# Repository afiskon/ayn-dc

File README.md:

# AYN/DC

QRP CW Transceiver

* Covers 40, 30, 20 and 17 meters
* Easily modifiable for other 4 bands
* DC receiver with sideband suppression
* Simple but effective AGC
* Supports RIT and XIT
* 10-30 WPM Elekey-B type keyer + straight key mode
* Keyer settings are saved in EEPROM
* ~5W class C power amplifier
* Has a VCC indicator and a SWR meter
* PCB is designed to fit into Hammond 1590BB enclosure
* The project is 100% open-source

Links:

* Article (in Russian): https://eax.me/2023/2023-01-16-ayn-dc-transceiver.html
* Demo: https://www.youtube.com/watch?v=9x_RN68QJhk

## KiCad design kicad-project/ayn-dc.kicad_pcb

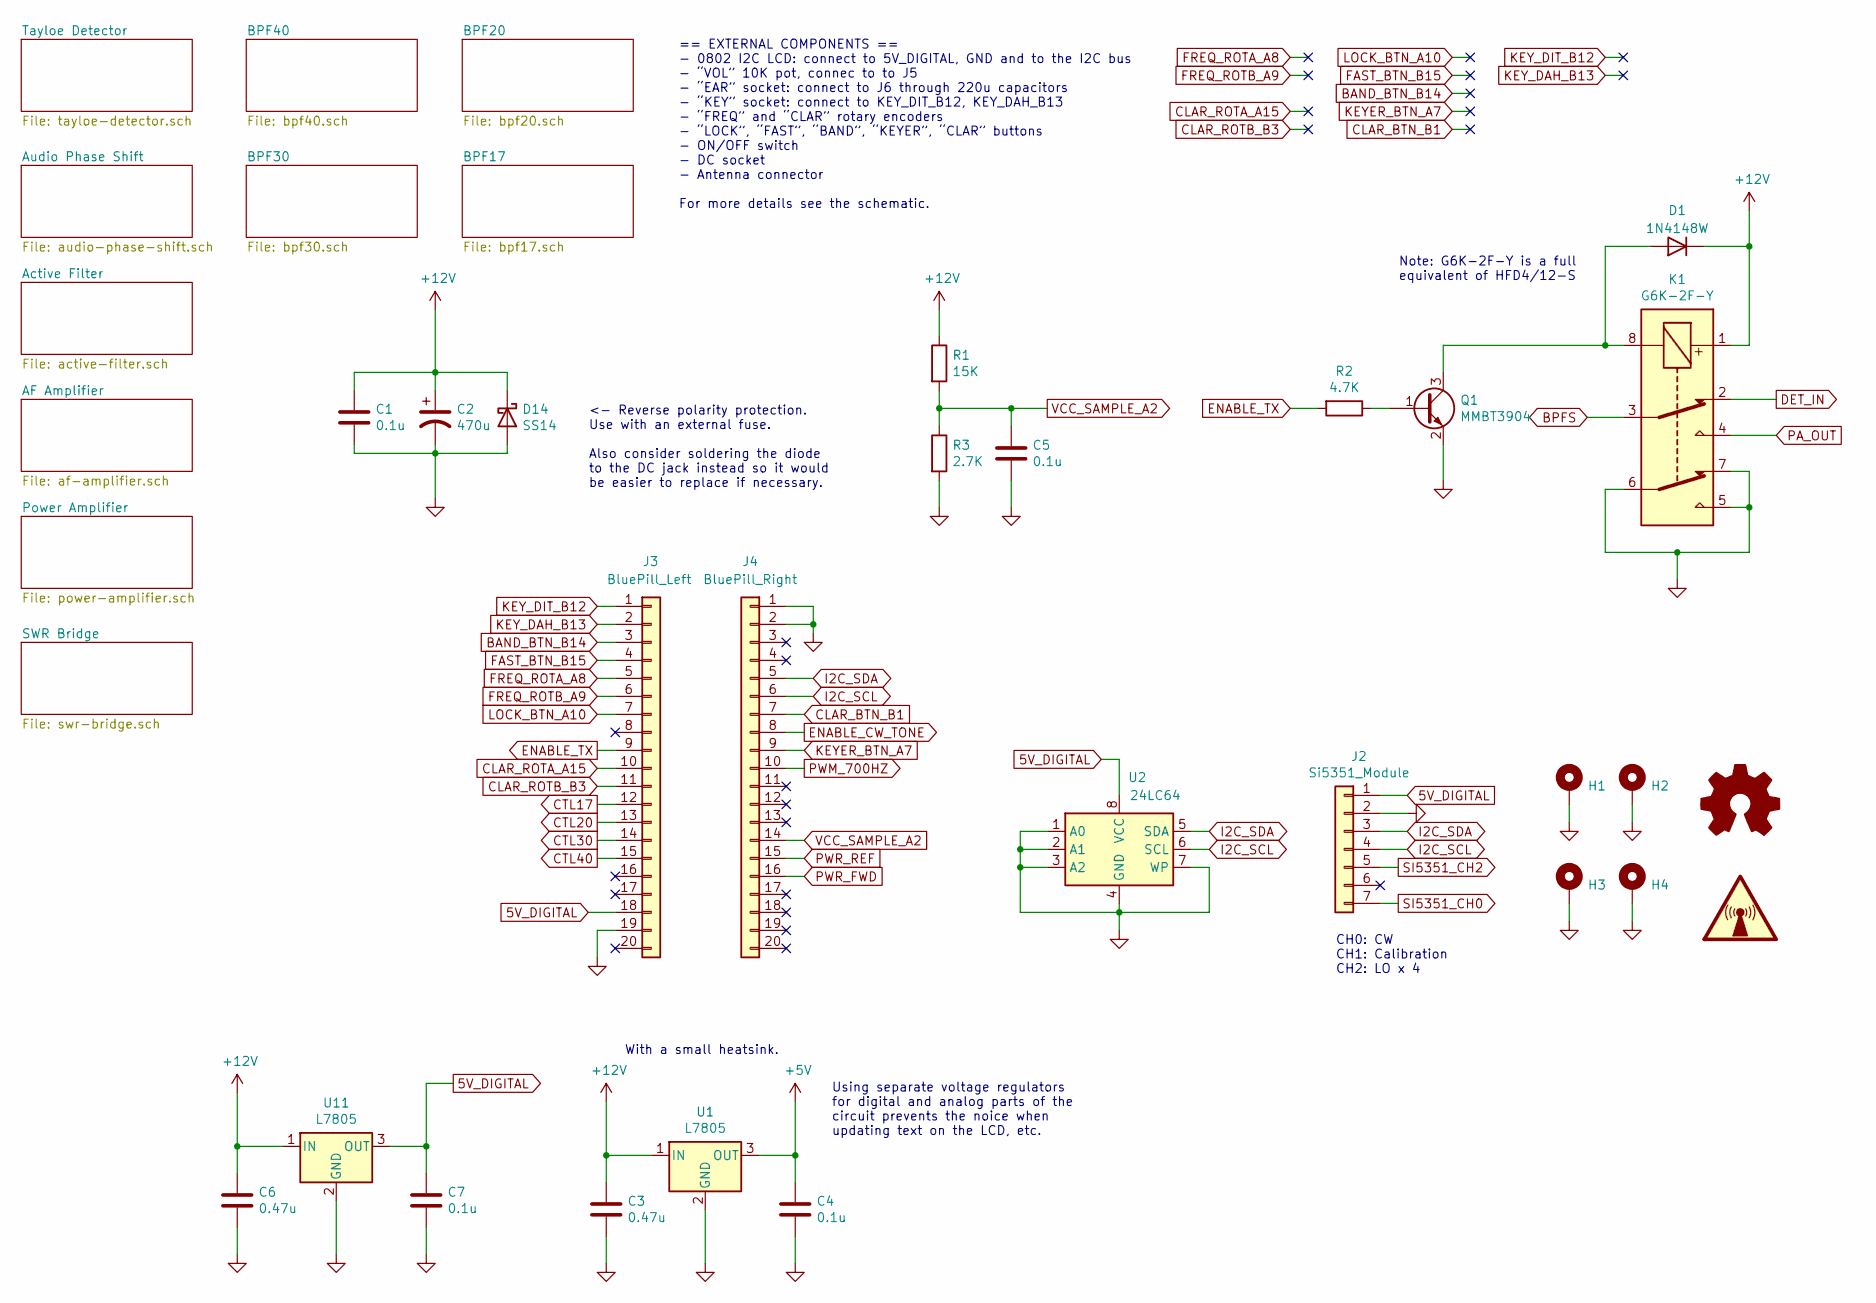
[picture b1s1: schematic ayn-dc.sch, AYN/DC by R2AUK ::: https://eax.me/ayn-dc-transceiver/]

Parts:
C1, C4, C5, C7: 0.1u; C_0805_2012Metric_Pad1.15x1.40mm_HandSolder
C2: 470u; PinSocket_1x02_P2.54mm_Vertical
C3, C6: 0.47u; C_0805_2012Metric_Pad1.15x1.40mm_HandSolder
D1: 1N4148W; D_SOD-123
D14: SS14; D_SMA_Handsoldering
H1, H2, H3, H4: MountingHole_Pad; MountingHole_3mm_Pad
J2: Si5351_Module; PinSocket_1x07_P2.54mm_Vertical
J3: BluePill_Left; PinSocket_1x20_P2.54mm_Vertical
J4: BluePill_Right; PinSocket_1x20_P2.54mm_Vertical
K1: G6K-2F-Y; Relay_DPDT_Omron_G6K-2F-Y
Q1: MMBT3904; SOT-23
R1: 15K; R_0805_2012Metric_Pad1.15x1.40mm_HandSolder
R2: 4.7K; R_0805_2012Metric_Pad1.15x1.40mm_HandSolder
R3: 2.7K; R_0805_2012Metric_Pad1.15x1.40mm_HandSolder
SYM1: Logo_Open_Hardware_Small; OSHW-Logo2_9.8x8mm_SilkScreen
SYM2: SYM_Radio_Waves_Large; KiCad-Logo_5mm_SilkScreen
U1: L7805; TO-220-3_Vertical
U2: 24LC64; SO-8_5.3x6.2mm_P1.27mm
U11: L7805; TO-263-2

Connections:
5V_DIGITAL: C7.1, J2.1, J3.18, U2.8 (VCC), U11.3 (OUT)
+5V: C4.1, U1.3 (OUT); also elsewhere on the board
+12V: C1.1, C2.1, C3.1, C6.1, D1.1 (K), D14.1 (K), K1.1, R1.1, U1.1 (IN), U11.1 (IN); also elsewhere on the board
BAND_BTN_B14: J3.3
BPFS: K1.3; also elsewhere on the board
CLAR_BTN_B1: J4.7
CLAR_ROTA_A15: J3.10
CLAR_ROTB_B3: J3.11
CTL17: J3.12; also elsewhere on the board
CTL20: J3.13; also elsewhere on the board
CTL30: J3.14; also elsewhere on the board
CTL40: J3.15; also elsewhere on the board
DET_IN: K1.2; also elsewhere on the board
ENABLE_CW_TONE: J4.8; also elsewhere on the board
ENABLE_TX: J3.9, R2.2; also elsewhere on the board
FAST_BTN_B15: J3.4
FREQ_ROTA_A8: J3.5
FREQ_ROTB_A9: J3.6
GND: C1.2, C2.2, C3.2, C4.2, C5.2, C6.2, C7.2, D14.2 (A), H1.1, H2.1, H3.1, H4.1, J2.2, J3.19, J4.1, J4.2, K1.5, K1.6, K1.7, Q1.2 (E), R3.2, U1.2 (GND), U2.1 (A0), U2.2 (A1), U2.3 (A2), U2.4 (GND), U2.7 (WP), U11.2 (GND); also elsewhere on the board
I2C_SCL: J2.4, J4.6, U2.6 (SCL)
I2C_SDA: J2.3, J4.5, U2.5 (SDA)
KEYER_BTN_A7: J4.9
KEY_DAH_B13: J3.2
KEY_DIT_B12: J3.1
LOCK_BTN_A10: J3.7
unnamed: D1.2 (A), K1.8, Q1.3 (C)
unnamed: Q1.1 (B), R2.1
PA_OUT: K1.4; also elsewhere on the board
PWM_700HZ: J4.10; also elsewhere on the board
PWR_FWD: J4.16; also elsewhere on the board
PWR_REF: J4.15; also elsewhere on the board
SI5351_CH0: J2.7; also elsewhere on the board
SI5351_CH2: J2.5; also elsewhere on the board
VCC_SAMPLE_A2: C5.1, J4.14, R1.2, R3.1

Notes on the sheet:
CH0: CW CH1: Calibration CH2: LO x 4
== EXTERNAL COMPONENTS == - 0802 I2C LCD: connect to 5V_DIGITAL, GND and to the I2C bus - “VOL” 10K pot, connec to to J5 - “EAR” socket: connect to J6 through 220u capacitors - “KEY” socket: connect to KEY_DIT_B12, KEY_DAH_B13 - “FREQ” and “CLAR” rotary encoders - “LOCK”, “FAST”, “BAND”, “KEYER”, “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
With a small heatsink.
Note: G6K-2F-Y is a full equivalent of HFD4/12-S
<- Reverse polarity protection. Use with an external fuse. Also consider soldering the diode to the DC jack instead so it would be easier to replace if necessary.
Using separate voltage regulators for digital and analog parts of the circuit prevents the noice when updating text on the LCD, etc.

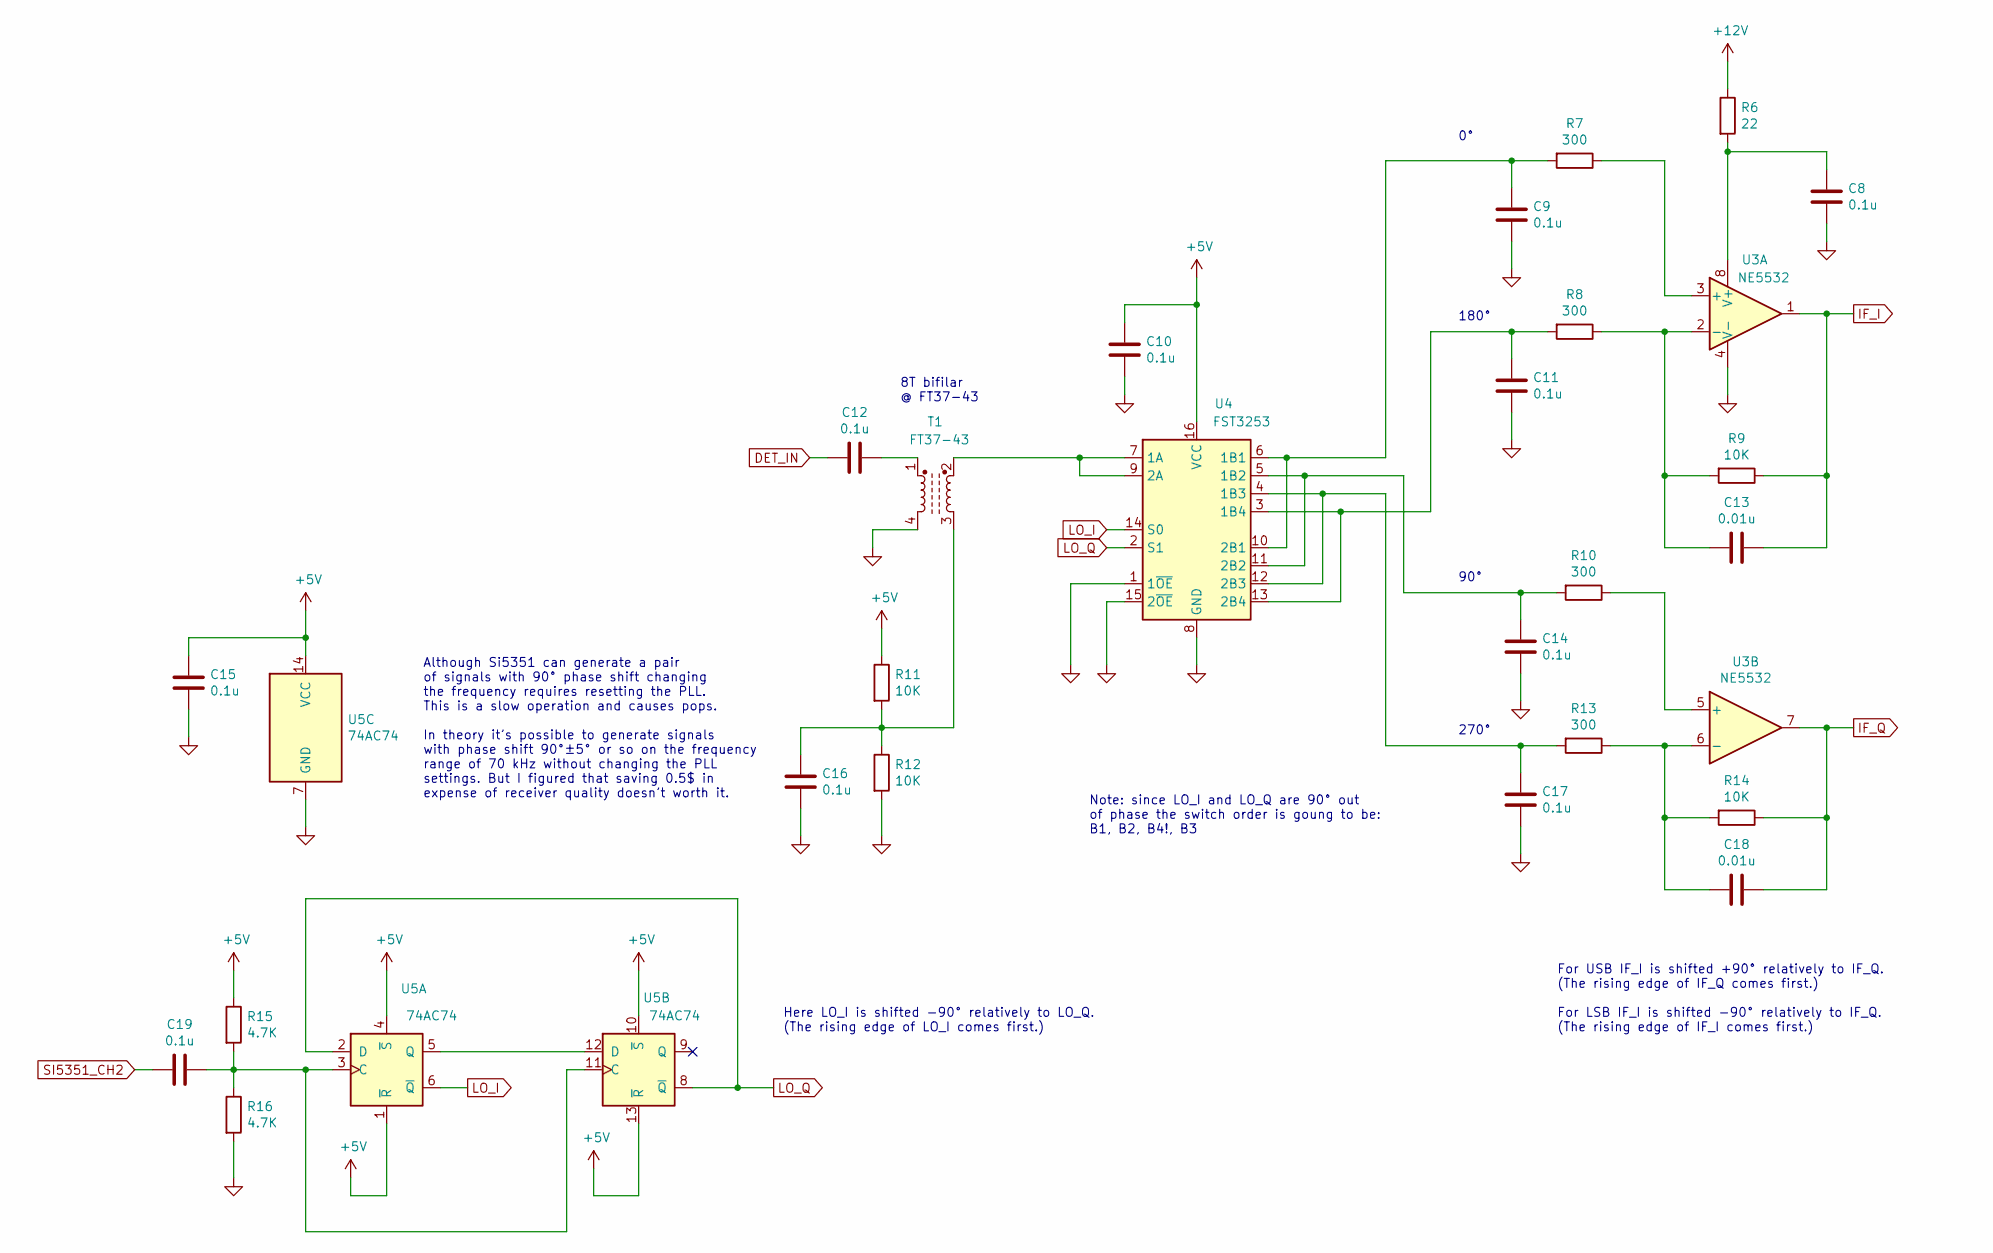
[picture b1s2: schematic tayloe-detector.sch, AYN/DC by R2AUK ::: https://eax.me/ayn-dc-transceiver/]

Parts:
C8, C9, C10, C11, C12, C14, C15, C16, C17, C19: 0.1u; C_0805_2012Metric_Pad1.15x1.40mm_HandSolder
C13, C18: 0.01u; C_0805_2012Metric_Pad1.15x1.40mm_HandSolder
R6: 22; R_0805_2012Metric_Pad1.15x1.40mm_HandSolder
R7, R8, R10, R13: 300; R_0805_2012Metric_Pad1.15x1.40mm_HandSolder
R9, R11, R12, R14: 10K; R_0805_2012Metric_Pad1.15x1.40mm_HandSolder
R15, R16: 4.7K; R_0805_2012Metric_Pad1.15x1.40mm_HandSolder
T1: FT37-43; DIP-4_W7.62mm
U3: NE5532; SOIC-8_5.23x5.23mm_P1.27mm
U4: FST3253; TSSOP-16_4.4x5mm_P0.65mm
U5: 74AC74; SOIC-14_3.9x8.7mm_P1.27mm

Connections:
+5V: C10.1, C15.1, R11.1, R15.1, U4.16 (VCC), U5.1 (~R), U5.4 (~S), U5.10 (~S), U5.13 (~R), U5.14 (VCC); also elsewhere on the board
+12V: R6.1; also elsewhere on the board
DET_IN: C12.2; also elsewhere on the board
GND: C8.2, C9.2, C10.2, C11.2, C14.2, C15.2, C16.2, C17.2, R12.2, R16.2, T1.4, U3.4 (V-), U4.1 (1~OE), U4.8 (GND), U4.15 (2~OE), U5.7 (GND); also elsewhere on the board
IF_I: C13.1, R9.1, U3.1; also elsewhere on the board
IF_Q: C18.1, R14.1, U3.7; also elsewhere on the board
LO_I: U4.14 (S0), U5.6 (~Q)
LO_Q: U4.2 (S1), U5.2 (D), U5.8 (~Q)
unnamed: C8.1, R6.2, U3.8 (V+)
unnamed: C9.1, R7.2, U4.6 (1B1), U4.10 (2B1)
unnamed: C11.1, R8.2, U4.3 (1B4), U4.13 (2B4)
unnamed: C12.1, T1.1
unnamed: C13.2, R8.1, R9.2, U3.2 (-)
unnamed: C14.1, R10.2, U4.5 (1B2), U4.11 (2B2)
unnamed: C16.1, R11.2, R12.1, T1.3
unnamed: C17.1, R13.2, U4.4 (1B3), U4.12 (2B3)
unnamed: C18.2, R13.1, R14.2, U3.6 (-)
unnamed: C19.1, R15.2, R16.1, U5.3 (C), U5.11 (C)
unnamed: R7.1, U3.3 (+)
unnamed: R10.1, U3.5 (+)
unnamed: T1.2, U4.7 (1A), U4.9 (2A)
unnamed: U5.5 (Q), U5.12 (D)
SI5351_CH2: C19.2; also elsewhere on the board

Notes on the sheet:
Although Si5351 can generate a pair of signals with 90° phase shift changing the frequency requires resetting the PLL. This is a slow operation and causes pops. In theory it’s possible to generate signals with phase shift 90°±5° or so on the frequency range of 70 kHz without changing the PLL settin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
180°
90°
270°
Note: since LO_I and LO_Q are 90° out of phase the switch order is goung to be: B1, B2, B4!, B3
8T bifilar @ FT37-43
Here LO_I is shifted -90° relatively to LO_Q. (The rising edge of LO_I comes first.)
For USB IF_I is shifted +90° relatively to IF_Q. (The rising edge of IF_Q comes first.) For LSB IF_I is shifted -90° relatively to IF_Q. (The rising edge of IF_I comes first.)

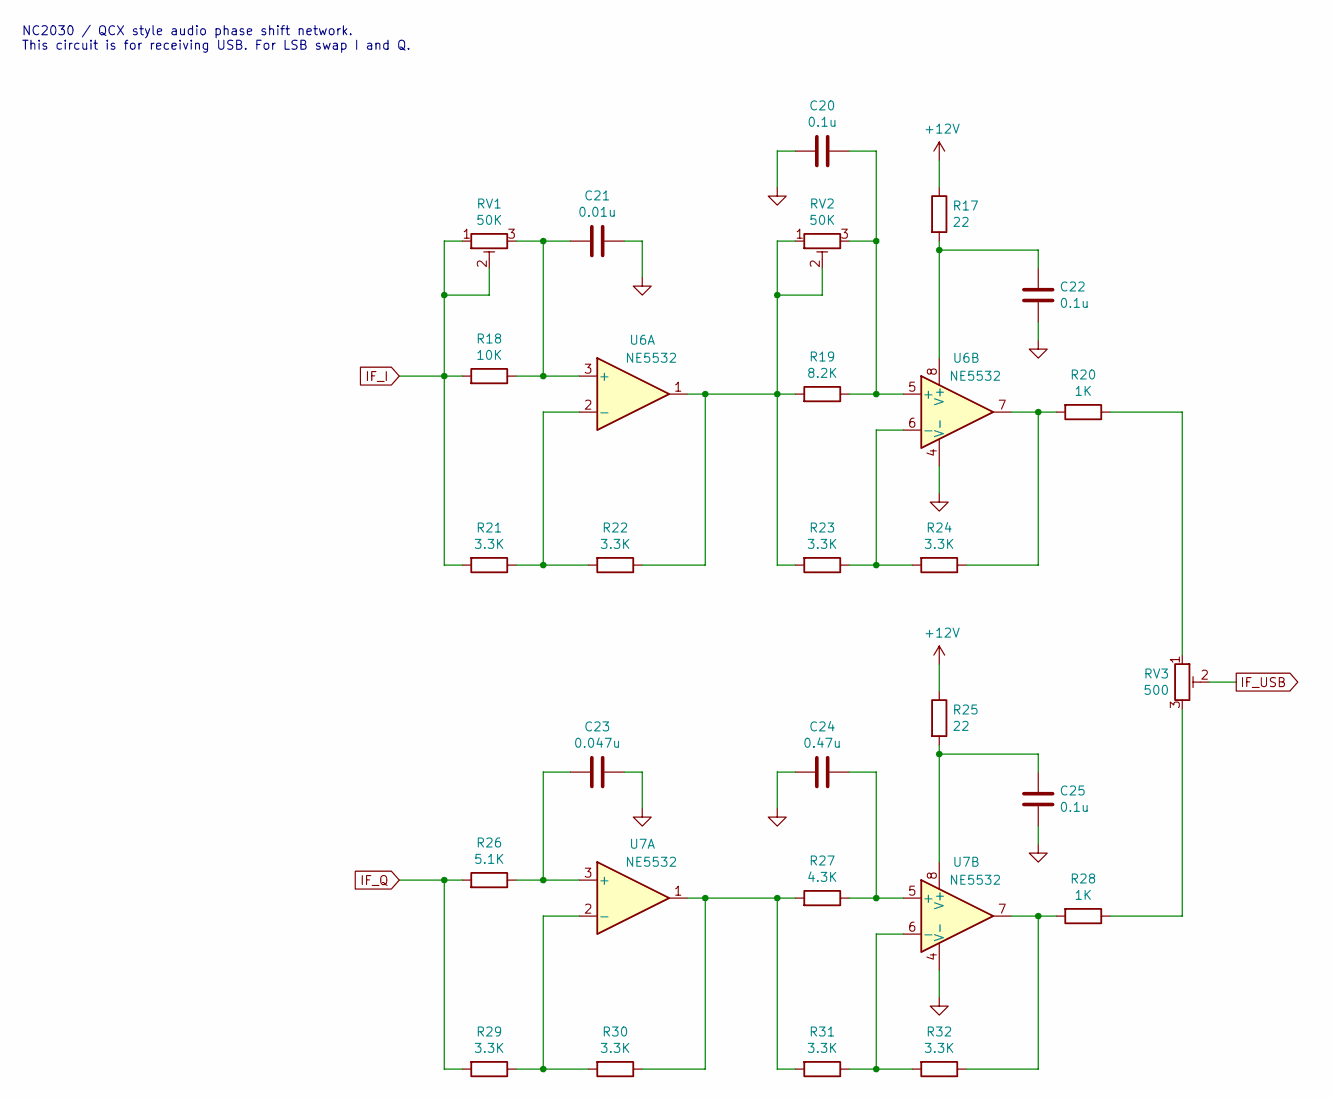
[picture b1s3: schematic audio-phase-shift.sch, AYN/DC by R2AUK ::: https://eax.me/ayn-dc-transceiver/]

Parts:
C20, C22, C25: 0.1u; C_0805_2012Metric_Pad1.15x1.40mm_HandSolder
C21: 0.01u; C_0805_2012Metric_Pad1.15x1.40mm_HandSolder
C23: 0.047u; C_0805_2012Metric_Pad1.15x1.40mm_HandSolder
C24: 0.47u; C_0805_2012Metric_Pad1.15x1.40mm_HandSolder
R17, R25: 22; R_0805_2012Metric_Pad1.15x1.40mm_HandSolder
R18: 10K; R_0805_2012Metric_Pad1.15x1.40mm_HandSolder
R19: 8.2K; R_0805_2012Metric_Pad1.15x1.40mm_HandSolder
R20, R28: 1K; R_0805_2012Metric_Pad1.15x1.40mm_HandSolder
R21, R22, R23, R24, R29, R30, R31, R32: 3.3K; R_0805_2012Metric_Pad1.15x1.40mm_HandSolder
R26: 5.1K; R_0805_2012Metric_Pad1.15x1.40mm_HandSolder
R27: 4.3K; R_0805_2012Metric_Pad1.15x1.40mm_HandSolder
RV1, RV2: 50K; Potentiometer_Bourns_3296W_Vertical
RV3: 500; Potentiometer_Bourns_3296W_Vertical
U6, U7: NE5532; SOIC-8_5.23x5.23mm_P1.27mm

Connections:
+12V: R17.1, R25.1; also elsewhere on the board
GND: C20.2, C21.1, C22.2, C23.1, C24.2, C25.2, U6.4 (V-), U7.4 (V-); also elsewhere on the board
IF_I: R18.2, R21.2, RV1.1, RV1.2; also elsewhere on the board
IF_Q: R26.2, R29.2; also elsewhere on the board
IF_USB: RV3.2; also elsewhere on the board
unnamed: C20.1, R19.1, RV2.3, U6.5 (+)
unnamed: C21.2, R18.1, RV1.3, U6.3 (+)
unnamed: C22.1, R17.2, U6.8 (V+)
unnamed: C23.2, R26.1, U7.3 (+)
unnamed: C24.1, R27.1, U7.5 (+)
unnamed: C25.1, R25.2, U7.8 (V+)
unnamed: R19.2, R22.1, R23.2, RV2.1, RV2.2, U6.1
unnamed: R20.1, RV3.1
unnamed: R20.2, R24.1, U6.7
unnamed: R21.1, R22.2, U6.2 (-)
unnamed: R23.1, R24.2, U6.6 (-)
unnamed: R27.2, R30.1, R31.2, U7.1
unnamed: R28.1, RV3.3
unnamed: R28.2, R32.1, U7.7
unnamed: R29.1, R30.2, U7.2 (-)
unnamed: R31.1, R32.2, U7.6 (-)

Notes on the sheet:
NC2030 / QCX style audio phase shift network. This circuit is for receiving USB. For LSB swap I and Q.

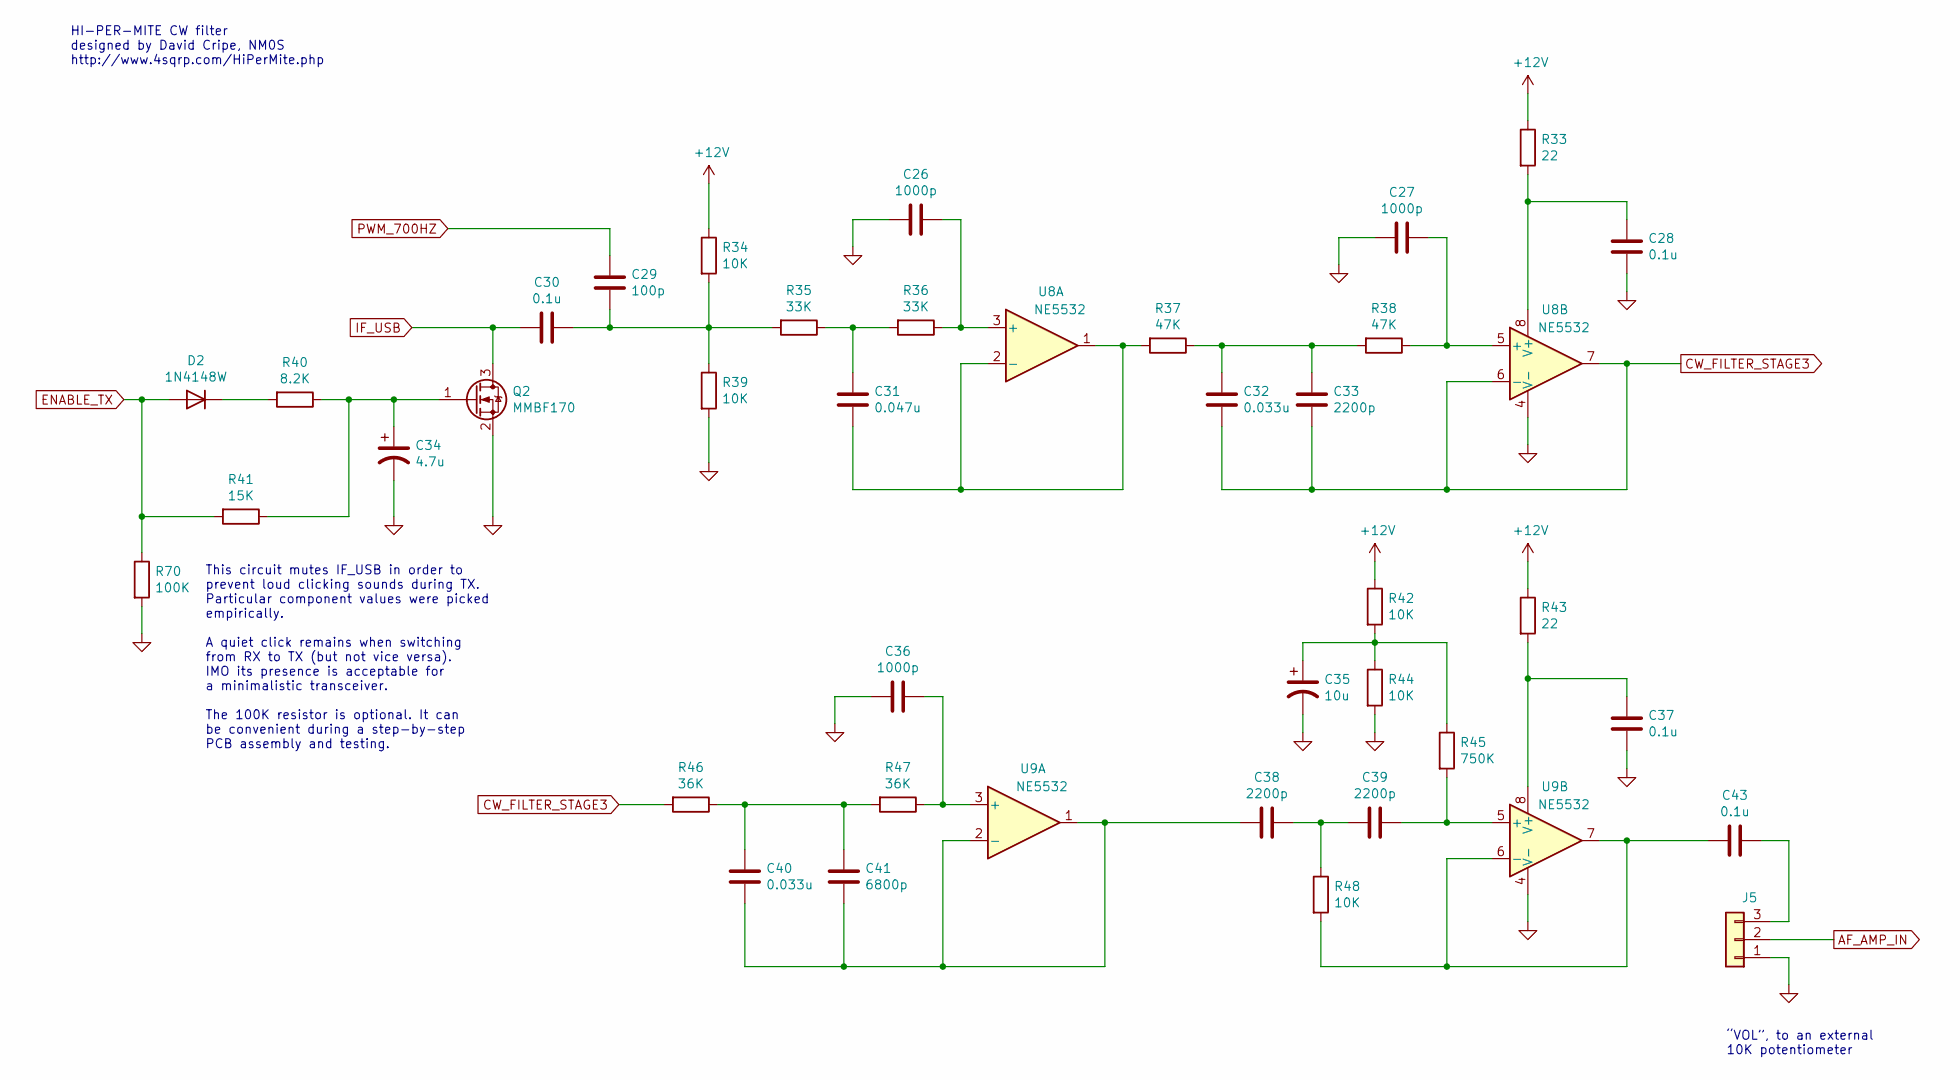
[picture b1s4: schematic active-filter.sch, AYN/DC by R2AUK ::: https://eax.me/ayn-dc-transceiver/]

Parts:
C26, C27, C36: 1000p; C_0805_2012Metric_Pad1.15x1.40mm_HandSolder
C28, C30, C37, C43: 0.1u; C_0805_2012Metric_Pad1.15x1.40mm_HandSolder
C29: 100p; C_0805_2012Metric_Pad1.15x1.40mm_HandSolder
C31: 0.047u; C_0805_2012Metric_Pad1.15x1.40mm_HandSolder
C32, C40: 0.033u; C_0805_2012Metric_Pad1.15x1.40mm_HandSolder
C33, C38, C39: 2200p; C_0805_2012Metric_Pad1.15x1.40mm_HandSolder
C34: 4.7u; CP_Elec_4x5.4
C35: 10u; CP_Elec_4x5.4
C41: 6800p; C_0805_2012Metric_Pad1.15x1.40mm_HandSolder
D2: 1N4148W; D_SOD-123
J5: Conn_01x03; PinSocket_1x03_P2.54mm_Vertical
Q2: MMBF170; SOT-23
R33, R43: 22; R_0805_2012Metric_Pad1.15x1.40mm_HandSolder
R34, R39, R42, R44, R48: 10K; R_0805_2012Metric_Pad1.15x1.40mm_HandSolder
R35, R36: 33K; R_0805_2012Metric_Pad1.15x1.40mm_HandSolder
R37, R38: 47K; R_0805_2012Metric_Pad1.15x1.40mm_HandSolder
R40: 8.2K; R_0805_2012Metric_Pad1.15x1.40mm_HandSolder
R41: 15K; R_0805_2012Metric_Pad1.15x1.40mm_HandSolder
R45: 750K; R_0805_2012Metric_Pad1.15x1.40mm_HandSolder
R46, R47: 36K; R_0805_2012Metric_Pad1.15x1.40mm_HandSolder
R70: 100K; R_0805_2012Metric_Pad1.15x1.40mm_HandSolder
U8, U9: NE5532; SOIC-8_5.23x5.23mm_P1.27mm

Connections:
+12V: R33.1, R34.1, R42.1, R43.1; also elsewhere on the board
AF_AMP_IN: J5.2; also elsewhere on the board
CW_FILTER_STAGE3: C32.2, C33.2, R46.2, U8.6 (-), U8.7
ENABLE_TX: D2.2 (A), R41.2, R70.1; also elsewhere on the board
GND: C26.2, C27.2, C28.2, C34.2, C35.2, C36.2, C37.2, J5.1, Q2.2 (S), R39.2, R44.2, R70.2, U8.4 (V-), U9.4 (V-); also elsewhere on the board
IF_USB: C30.2, Q2.3 (D); also elsewhere on the board
unnamed: C26.1, R36.1, U8.3 (+)
unnamed: C27.1, R38.1, U8.5 (+)
unnamed: C28.1, R33.2, U8.8 (V+)
unnamed: C29.2, C30.1, R34.2, R35.2, R39.1
unnamed: C31.1, R35.1, R36.2
unnamed: C31.2, R37.2, U8.1, U8.2 (-)
unnamed: C32.1, C33.1, R37.1, R38.2
unnamed: C34.1, Q2.1 (G), R40.1, R41.1
unnamed: C35.1, R42.2, R44.1, R45.1
unnamed: C36.1, R47.1, U9.3 (+)
unnamed: C37.1, R43.2, U9.8 (V+)
unnamed: C38.1, C39.2, R48.1
unnamed: C38.2, C40.2, C41.2, U9.1, U9.2 (-)
unnamed: C39.1, R45.2, U9.5 (+)
unnamed: C40.1, C41.1, R46.1, R47.2
unnamed: C43.1, J5.3
unnamed: C43.2, R48.2, U9.6 (-), U9.7
unnamed: D2.1 (K), R40.2
PWM_700HZ: C29.1; also elsewhere on the board

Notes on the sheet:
HI-PER-MITE CW filter designed by David Cripe, NM0S http://www.4sqrp.com/HiPerMite.php
“VOL”, to an external 10K potentiometer
This circuit mutes IF_USB in order to prevent loud clicking sounds during TX. Particular component values were picked empirically. A quiet click remains when switching from RX to TX (but not vice versa). IMO its presence is acceptable for a minimalistic transceiver. The 100K resistor is optional. I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

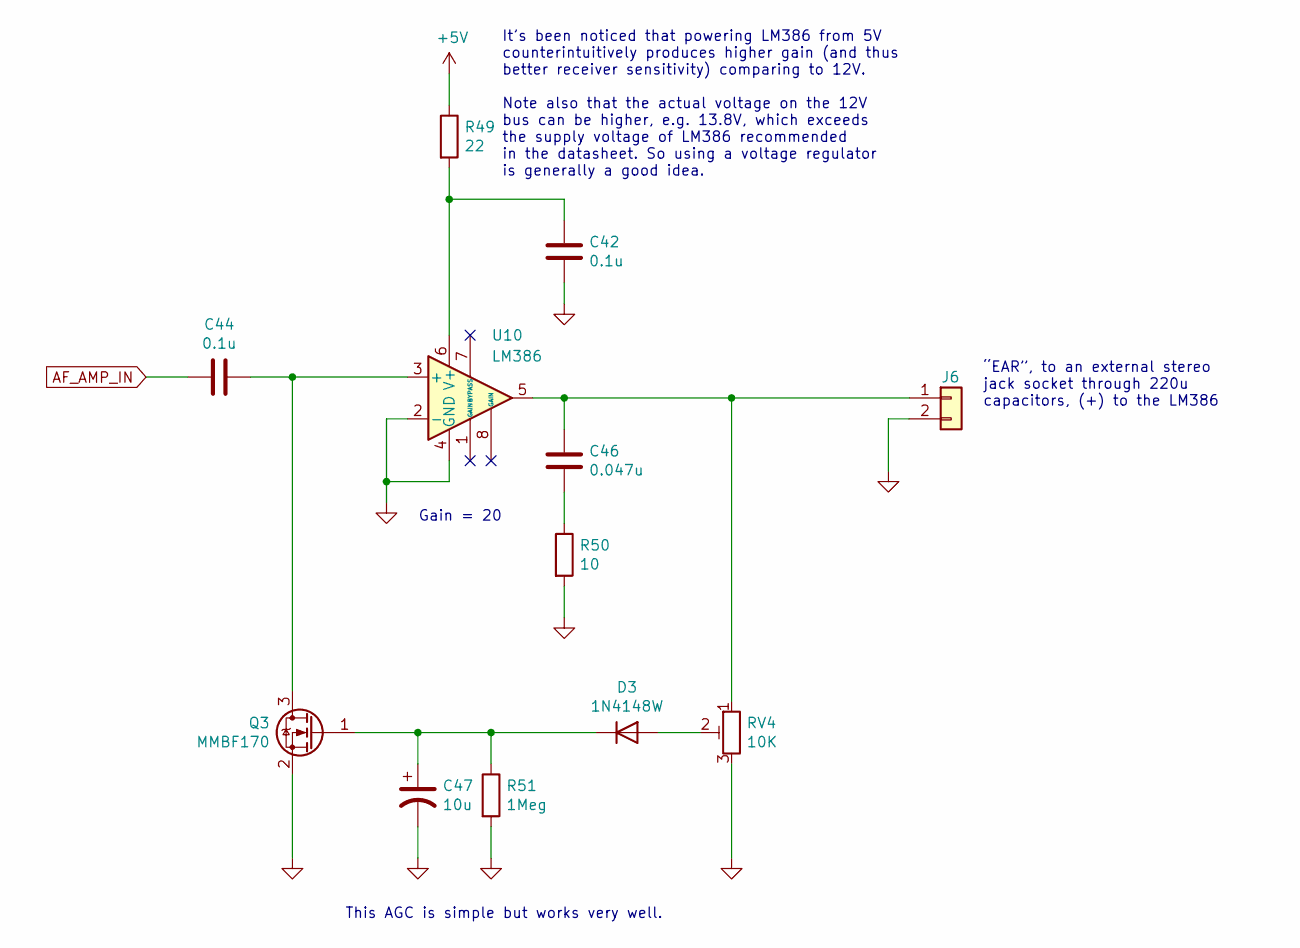
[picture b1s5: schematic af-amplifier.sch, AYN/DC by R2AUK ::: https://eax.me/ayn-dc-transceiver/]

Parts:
C42, C44: 0.1u; C_0805_2012Metric_Pad1.15x1.40mm_HandSolder
C46: 0.047u; C_0805_2012Metric_Pad1.15x1.40mm_HandSolder
C47: 10u; CP_Elec_4x5.4
D3: 1N4148W; D_SOD-123
J6: Conn_01x02; PinSocket_1x02_P2.54mm_Vertical
Q3: MMBF170; SOT-23
R49: 22; R_0805_2012Metric_Pad1.15x1.40mm_HandSolder
R50: 10; R_0805_2012Metric_Pad1.15x1.40mm_HandSolder
R51: 1Meg; R_0805_2012Metric_Pad1.15x1.40mm_HandSolder
RV4: 10K; Potentiometer_Bourns_3296W_Vertical
U10: LM386; SO-8_5.3x6.2mm_P1.27mm

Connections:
+5V: R49.1; also elsewhere on the board
AF_AMP_IN: C44.2; also elsewhere on the board
GND: C42.2, C47.2, J6.2, Q3.2 (S), R50.2, R51.2, RV4.3, U10.2 (-), U10.4 (GND); also elsewhere on the board
unnamed: C42.1, R49.2, U10.6 (V+)
unnamed: C44.1, Q3.3 (D), U10.3 (+)
unnamed: C46.1, J6.1, RV4.1, U10.5
unnamed: C46.2, R50.1
unnamed: C47.1, D3.1 (K), Q3.1 (G), R51.1
unnamed: D3.2 (A), RV4.2

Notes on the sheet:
“EAR”, to an external stereo jack socket through 220u capacitors, (+) to the LM386
It’s been noticed that powering LM386 from 5V counterintuitively produces higher gain (and thus better receiver sensitivity) comparing to 12V. Note also that the actual voltage on the 12V bus can be higher, e.g. 13.8V, which exceeds the supply voltage of LM386 recommended in the datasheet. So using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
Gain = 20
This AGC is simple but works very well.

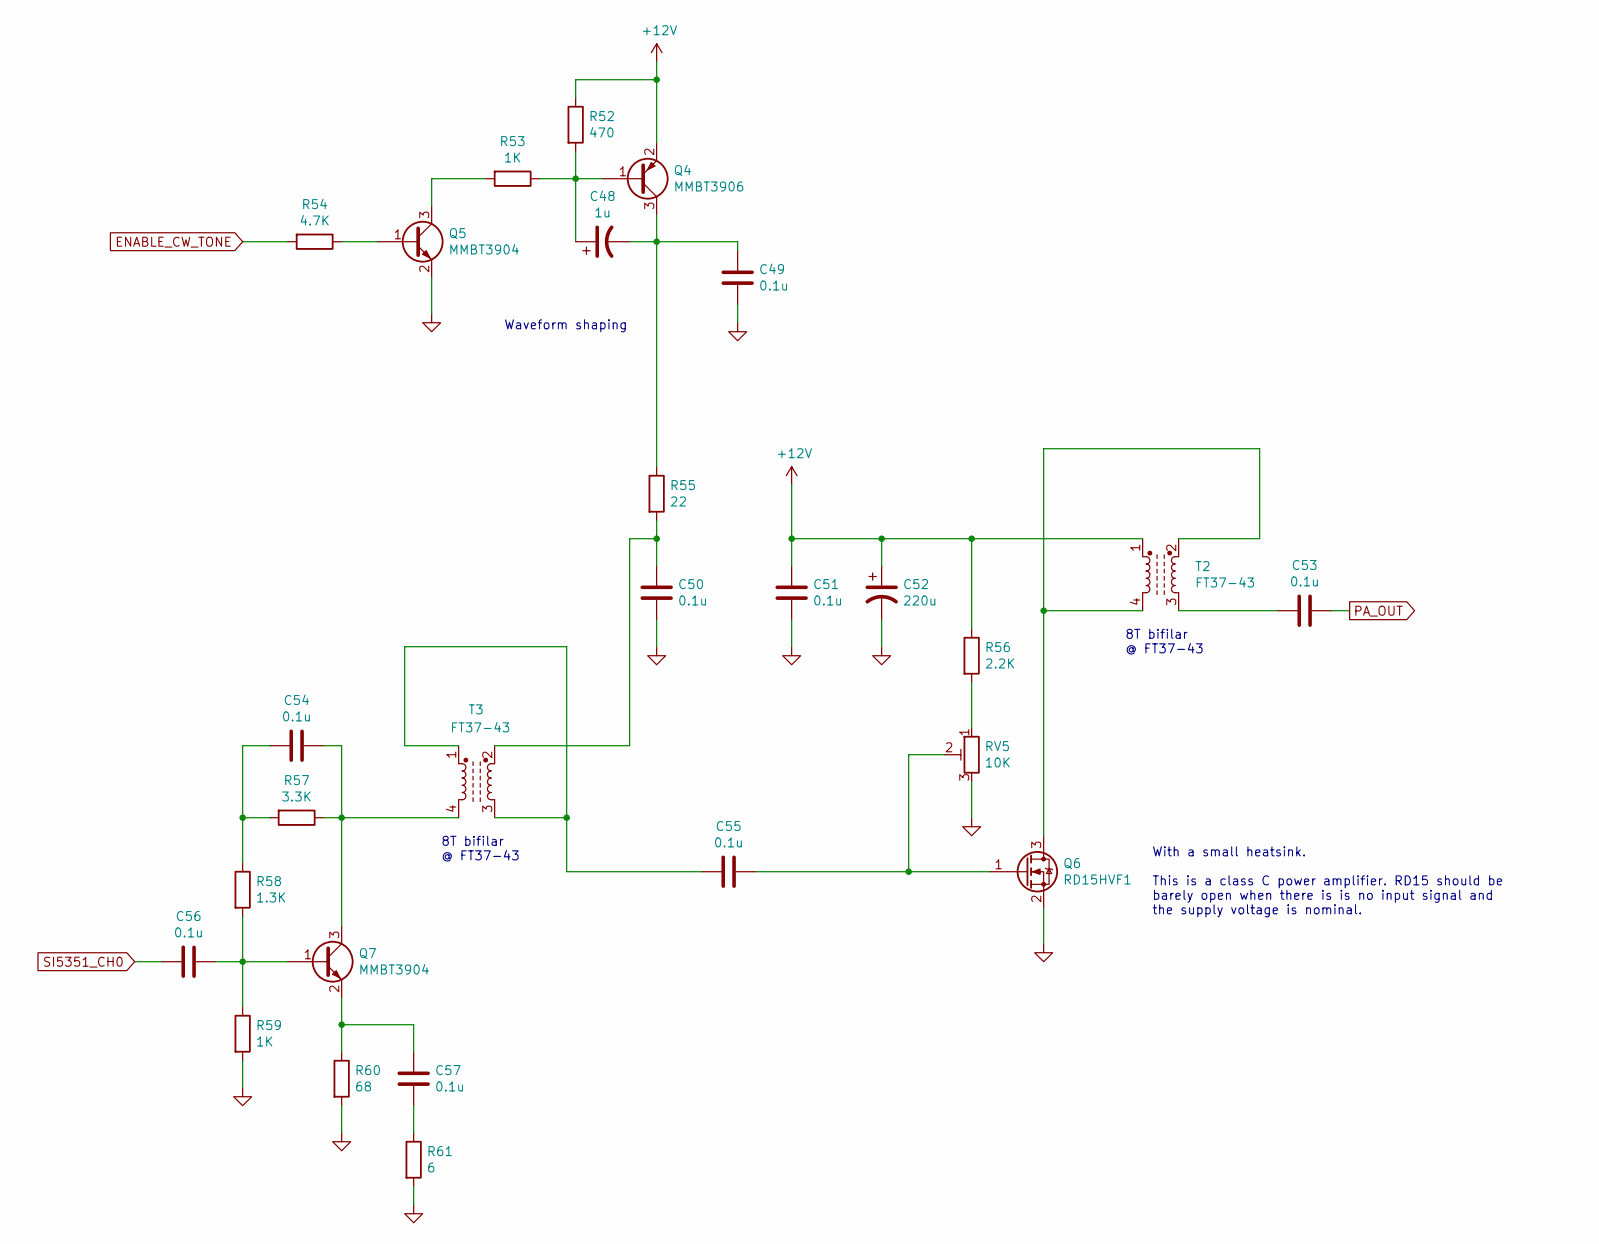
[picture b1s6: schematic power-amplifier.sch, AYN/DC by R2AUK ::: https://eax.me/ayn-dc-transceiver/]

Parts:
C48: 1u; CP_Elec_4x5.4
C49, C50, C51, C53, C54, C55, C56, C57: 0.1u; C_0805_2012Metric_Pad1.15x1.40mm_HandSolder
C52: 220u; CP_Elec_8x10.5
Q4: MMBT3906; SOT-23
Q5, Q7: MMBT3904; SOT-23
Q6: RD15HVF1; TO-220-3_Vertical
R52: 470; R_0805_2012Metric_Pad1.15x1.40mm_HandSolder
R53, R59: 1K; R_0805_2012Metric_Pad1.15x1.40mm_HandSolder
R54: 4.7K; R_0805_2012Metric_Pad1.15x1.40mm_HandSolder
R55: 22; R_0805_2012Metric_Pad1.15x1.40mm_HandSolder
R56: 2.2K; R_0805_2012Metric_Pad1.15x1.40mm_HandSolder
R57: 3.3K; R_0805_2012Metric_Pad1.15x1.40mm_HandSolder
R58: 1.3K; R_0805_2012Metric_Pad1.15x1.40mm_HandSolder
R60: 68; R_0805_2012Metric_Pad1.15x1.40mm_HandSolder
R61: 6; R_0805_2012Metric_Pad1.15x1.40mm_HandSolder
RV5: 10K; Potentiometer_Bourns_3296W_Vertical
T2, T3: FT37-43; DIP-4_W7.62mm

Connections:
+12V: C51.1, C52.1, Q4.2 (E), R52.1, R56.1, T2.1; also elsewhere on the board
ENABLE_CW_TONE: R54.2; also elsewhere on the board
GND: C49.2, C50.2, C51.2, C52.2, Q5.2 (E), Q6.2 (S), R59.2, R60.2, R61.2, RV5.3; also elsewhere on the board
unnamed: C48.1, Q4.1 (B), R52.2, R53.1
unnamed: C48.2, C49.1, Q4.3 (C), R55.1
unnamed: C50.1, R55.2, T3.2
unnamed: C53.2, T2.3
unnamed: C54.1, Q7.3 (C), R57.1, T3.4
unnamed: C54.2, R57.2, R58.1
unnamed: C55.1, Q6.1 (G), RV5.2
unnamed: C55.2, T3.1, T3.3
unnamed: C56.1, Q7.1 (B), R58.2, R59.1
unnamed: C57.1, Q7.2 (E), R60.1
unnamed: C57.2, R61.1
unnamed: Q5.1 (B), R54.1
unnamed: Q5.3 (C), R53.2
unnamed: Q6.3 (D), T2.2, T2.4
unnamed: R56.2, RV5.1
PA_OUT: C53.1; also elsewhere on the board
SI5351_CH0: C56.2; also elsewhere on the board

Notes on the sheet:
8T bifilar @ FT37-43
With a small heatsink. This is a class C power amplifier. RD15 should be barely open when there is is no input signal and the supply voltage is nominal.
Waveform shaping

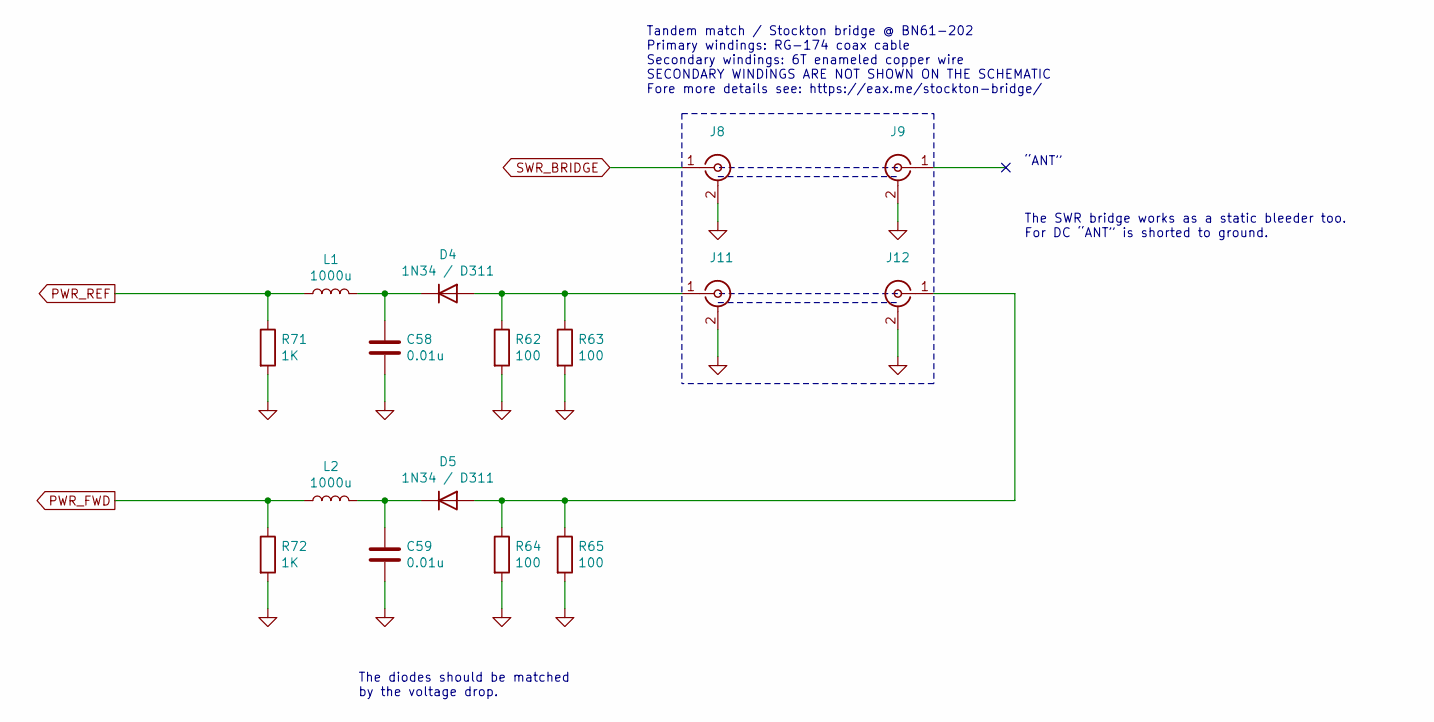
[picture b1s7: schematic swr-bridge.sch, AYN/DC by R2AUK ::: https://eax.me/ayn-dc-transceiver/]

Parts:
C58, C59: 0.01u; C_0805_2012Metric_Pad1.15x1.40mm_HandSolder
D4, D5: 1N34 / D311; D_DO-41_SOD81_P3.81mm_Vertical_AnodeUp
J8, J9, J11, J12: Conn_Coaxial; PinSocket_1x02_P2.54mm_Vertical
L1, L2: 1000u; L_Axial_L6.6mm_D2.7mm_P10.16mm_Horizontal_Vishay_IM-2
R62, R63, R64, R65: 100; R_0805_2012Metric_Pad1.15x1.40mm_HandSolder
R71, R72: 1K; R_0805_2012Metric_Pad1.15x1.40mm_HandSolder

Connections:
GND: C58.2, C59.2, J8.2 (Ext), J9.2 (Ext), J11.2 (Ext), J12.2 (Ext), R62.2, R63.2, R64.2, R65.2, R71.2, R72.2; also elsewhere on the board
unnamed: C58.1, D4.1 (K), L1.2
unnamed: C59.1, D5.1 (K), L2.2
unnamed: D4.2 (A), J11.1 (In), R62.1, R63.1
unnamed: D5.2 (A), J12.1 (In), R64.1, R65.1
PWR_FWD: L2.1, R72.1; also elsewhere on the board
PWR_REF: L1.1, R71.1; also elsewhere on the board
SWR_BRIDGE: J8.1 (In); also elsewhere on the board

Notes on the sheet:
“ANT”
The SWR bridge works as a static bleeder too. For DC “ANT” is shorted to ground.
Tandem match / Stockton bridge @ BN61-202 Primary windings: RG-174 coax cable Secondary windings: 6T enameled copper wire SECONDARY WINDINGS ARE NOT SHOWN ON THE SCHEMATIC Fore more details see: https://eax.me/stockton-bridge/
The diodes should be matched by the voltage drop.

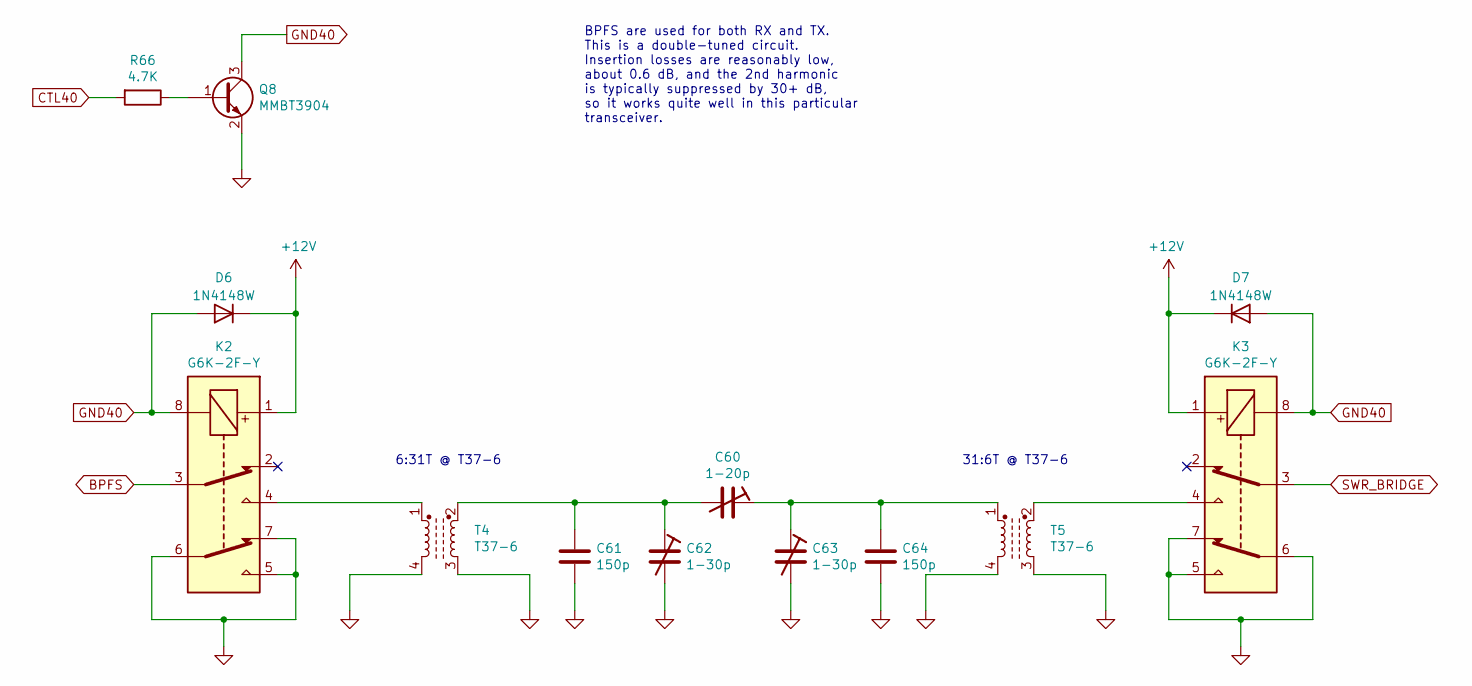
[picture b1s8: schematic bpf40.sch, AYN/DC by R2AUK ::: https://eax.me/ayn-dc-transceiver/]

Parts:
C60: 1-20p; C_Trim_THD_L7.0mm_W6.5mm_P5.00mm
C61, C64: 150p; C_0805_2012Metric_Pad1.15x1.40mm_HandSolder
C62, C63: 1-30p; C_Trim_THD_L7.0mm_W6.5mm_P5.00mm
D6, D7: 1N4148W; D_SOD-123
K2, K3: G6K-2F-Y; Relay_DPDT_Omron_G6K-2F-Y
Q8: MMBT3904; SOT-23
R66: 4.7K; R_0805_2012Metric_Pad1.15x1.40mm_HandSolder
T4, T5: T37-6; DIP-4_W7.62mm

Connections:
+12V: D6.1 (K), D7.1 (K), K2.1, K3.1; also elsewhere on the board
BPFS: K2.3; also elsewhere on the board
CTL40: R66.2; also elsewhere on the board
GND: C61.2, C62.2, C63.2, C64.2, K2.5, K2.6, K2.7, K3.5, K3.6, K3.7, Q8.2 (E), T4.3, T4.4, T5.3, T5.4; also elsewhere on the board
GND40: D6.2 (A), D7.2 (A), K2.8, K3.8, Q8.3 (C)
unnamed: C60.1, C63.1, C64.1, T5.1
unnamed: C60.2, C61.1, C62.1, T4.2
unnamed: K2.4, T4.1
unnamed: K3.4, T5.2
unnamed: Q8.1 (B), R66.1
SWR_BRIDGE: K3.3; also elsewhere on the board

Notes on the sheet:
6:31T @ T37-6
31:6T @ T37-6
BPFS are used for both RX and TX. This is a double-tuned circuit. Insertion losses are reasonably low, about 0.6 dB, and the 2nd harmonic is typically suppressed by 30+ dB, so it works quite well in this particular transceiver.
